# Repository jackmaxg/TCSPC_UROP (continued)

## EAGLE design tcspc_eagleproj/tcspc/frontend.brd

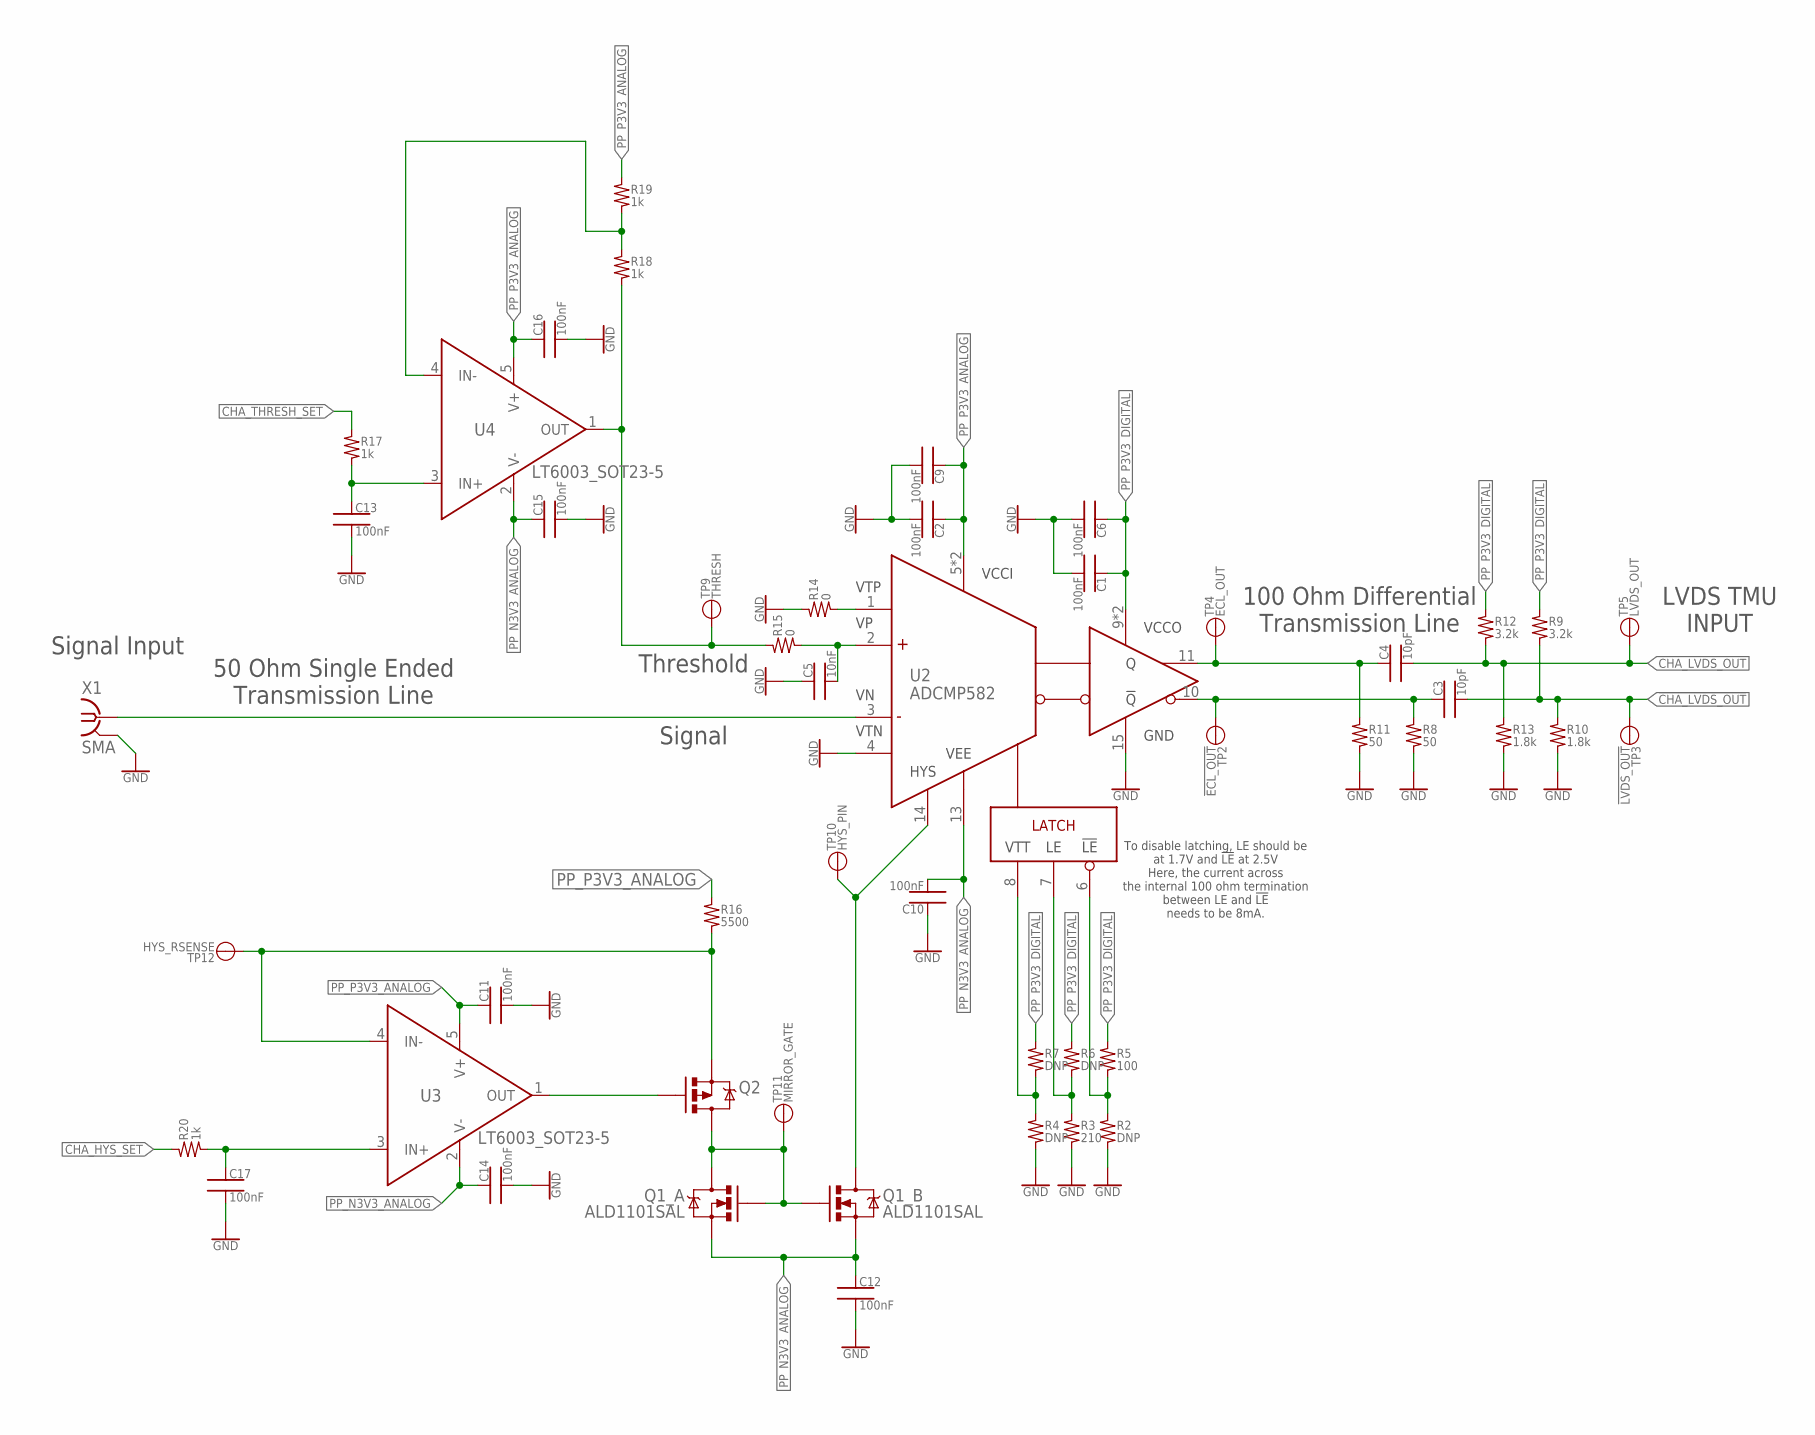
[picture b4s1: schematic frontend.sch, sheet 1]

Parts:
C1, C2, C6, C9, C10, C11, C12, C13, C14, C15, C16, C17: 100nF; 0402
C3, C4: 10pF; 0402
C5: 10nF; 0402
Q1: ALD1101SAL; SOIC_8
Q2: MOSFET_P-CHANNEL_SOT23-3; SOT23-3
R2, R4, R6, R7: DNP; 0402
R3: 210; 0402
R5: 100; 0402
R8, R11: 50; 0402
R9, R12: 3.2k; 0402
R10, R13: 1.8k; 0402
R14, R15: 0; 0402
R16: 5500; 0402
R17, R18, R19, R20: 1k; 0402
TP2: !ECL_OUT; TESTPOINT_PAD
TP3: !LVDS_OUT; TESTPOINT_PAD
TP4: ECL_OUT; TESTPOINT_PAD
TP5: LVDS_OUT; TESTPOINT_PAD
TP9: THRESH; 1X01
TP10: HYS_PIN; 1X01
TP11: MIRROR_GATE; 1X01
TP12: HYS_RSENSE; 1X01
U2: ADCMP582; QFN50P300X300X80-16N
U3, U4: LT6003_SOT23-5; SOT23-5
X1: SMA; J502-ND-142-0701-881/886

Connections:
!CHA_LVDS_OUT: C3.2, R9.2, R10.1, TP3.TP; also elsewhere on the board
CHA_HYS_SET: R20.1; also elsewhere on the board
CHA_LVDS_OUT: C4.2, R12.2, R13.1, TP5.TP; also elsewhere on the board
CHA_THRESH_SET: R17.1; also elsewhere on the board
GND: C1.2, C2.2, C5.1, C6.2, C9.2, C10.1, C11.2, C12.2, C13.2, C14.2, C15.2, C16.2, C17.2, R2.2, R3.2, R4.2, R8.2, R10.2, R11.2, R13.2, R14.1, U2.4 (VTN), U2.15 (GND), X1.G@1 (GND), X1.G@2 (GND), X1.G@3 (GND), X1.G@4 (GND); also elsewhere on the board
unnamed: Q2.2 (S), R16.2, TP12.1, U3.4 (IN-)
unnamed: Q1.2 (G), Q1.3 (D), Q1.6 (G), Q2.3 (D), TP11.1
unnamed: C3.1, R8.1, TP2.TP, U2.10 (!Q)
unnamed: C4.1, R11.1, TP4.TP, U2.11 (Q)
unnamed: R14.2, U2.1 (VTP)
unnamed: C13.1, R17.2, U4.3 (IN+)
unnamed: Q2.1 (G), U3.1 (OUT)
unnamed: R18.1, R19.2, U4.4 (IN-)
unnamed: R15.1, R18.2, TP9.1, U4.1 (OUT)
unnamed: C17.1, R20.2, U3.3 (IN+)
unnamed: U2.3 (VN), X1.1
unnamed: C5.2, R15.2, U2.2 (VP)
unnamed: R4.1, R7.2, U2.8 (VTT)
unnamed: R3.1, R6.2, U2.7 (LE)
unnamed: R2.1, R5.2, U2.6 (!LE)
unnamed: Q1.5 (D), TP10.1, U2.14 (HYS)
PP_N3V3_ANALOG: C10.2, C12.1, C14.1, C15.1, Q1.1 (S), Q1.7 (S), Q1.8 (S), U2.13 (VEE), U3.2 (V-), U4.2 (V-); also elsewhere on the board
PP_P3V3_ANALOG: C2.1, C9.1, C11.1, C16.1, R16.1, R19.1, U2.5 (VCCI), U2.16 (VCCI), U3.5 (V+), U4.5 (V+); also elsewhere on the board
PP_P3V3_DIGITAL: C1.1, C6.1, R5.1, R6.1, R7.1, R9.1, R12.1, U2.9 (VCCO), U2.12 (VCCO); also elsewhere on the board

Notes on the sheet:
LVDS TMU INPUT
Threshold
Signal Input
100 Ohm Differential Transmission Line
50 Ohm Single Ended Transmission Line
Signal
To disable latching, LE should be at 1.7V and !LE! at 2.5V Here, the current across the internal 100 ohm termination between LE and !LE! needs to be 8mA.

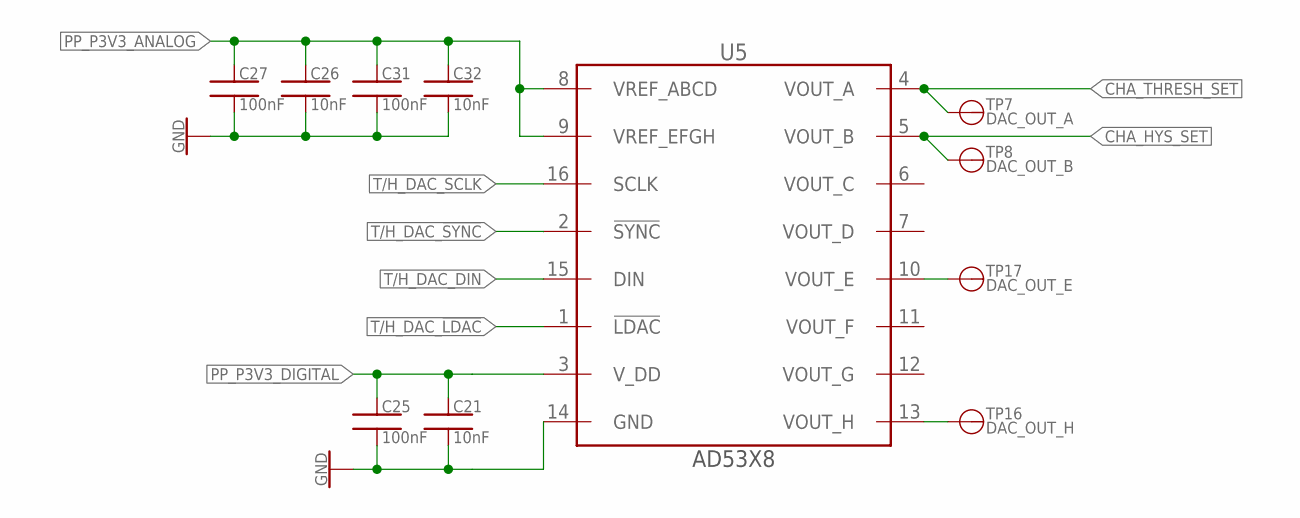
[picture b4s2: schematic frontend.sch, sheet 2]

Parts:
C21, C26, C32: 10nF; 0402
C25, C27, C31: 100nF; 0402
TP7: DAC_OUT_A; 1X01
TP8: DAC_OUT_B; 1X01
TP16: DAC_OUT_H; 1X01
TP17: DAC_OUT_E; 1X01
U5: AD53X8; TSSOP-16

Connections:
CHA_HYS_SET: TP8.1, U5.5 (VOUT_B); also elsewhere on the board
CHA_THRESH_SET: TP7.1, U5.4 (VOUT_A); also elsewhere on the board
GND: C21.2, C25.2, C26.2, C27.2, C31.2, C32.2, U5.14 (GND); also elsewhere on the board
unnamed: TP17.1, U5.10 (VOUT_E)
unnamed: TP16.1, U5.13 (VOUT_H)
PP_P3V3_ANALOG: C26.1, C27.1, C31.1, C32.1, U5.8 (VREF_ABCD), U5.9 (VREF_EFGH); also elsewhere on the board
PP_P3V3_DIGITAL: C21.1, C25.1, U5.3 (V_DD); also elsewhere on the board
T/H_DAC_!LDAC!: U5.1 (!LDAC); also elsewhere on the board
T/H_DAC_!SYNC!: U5.2 (!SYNC); also elsewhere on the board
T/H_DAC_DIN: U5.15 (DIN); also elsewhere on the board
T/H_DAC_SCLK: U5.16 (SCLK); also elsewhere on the board

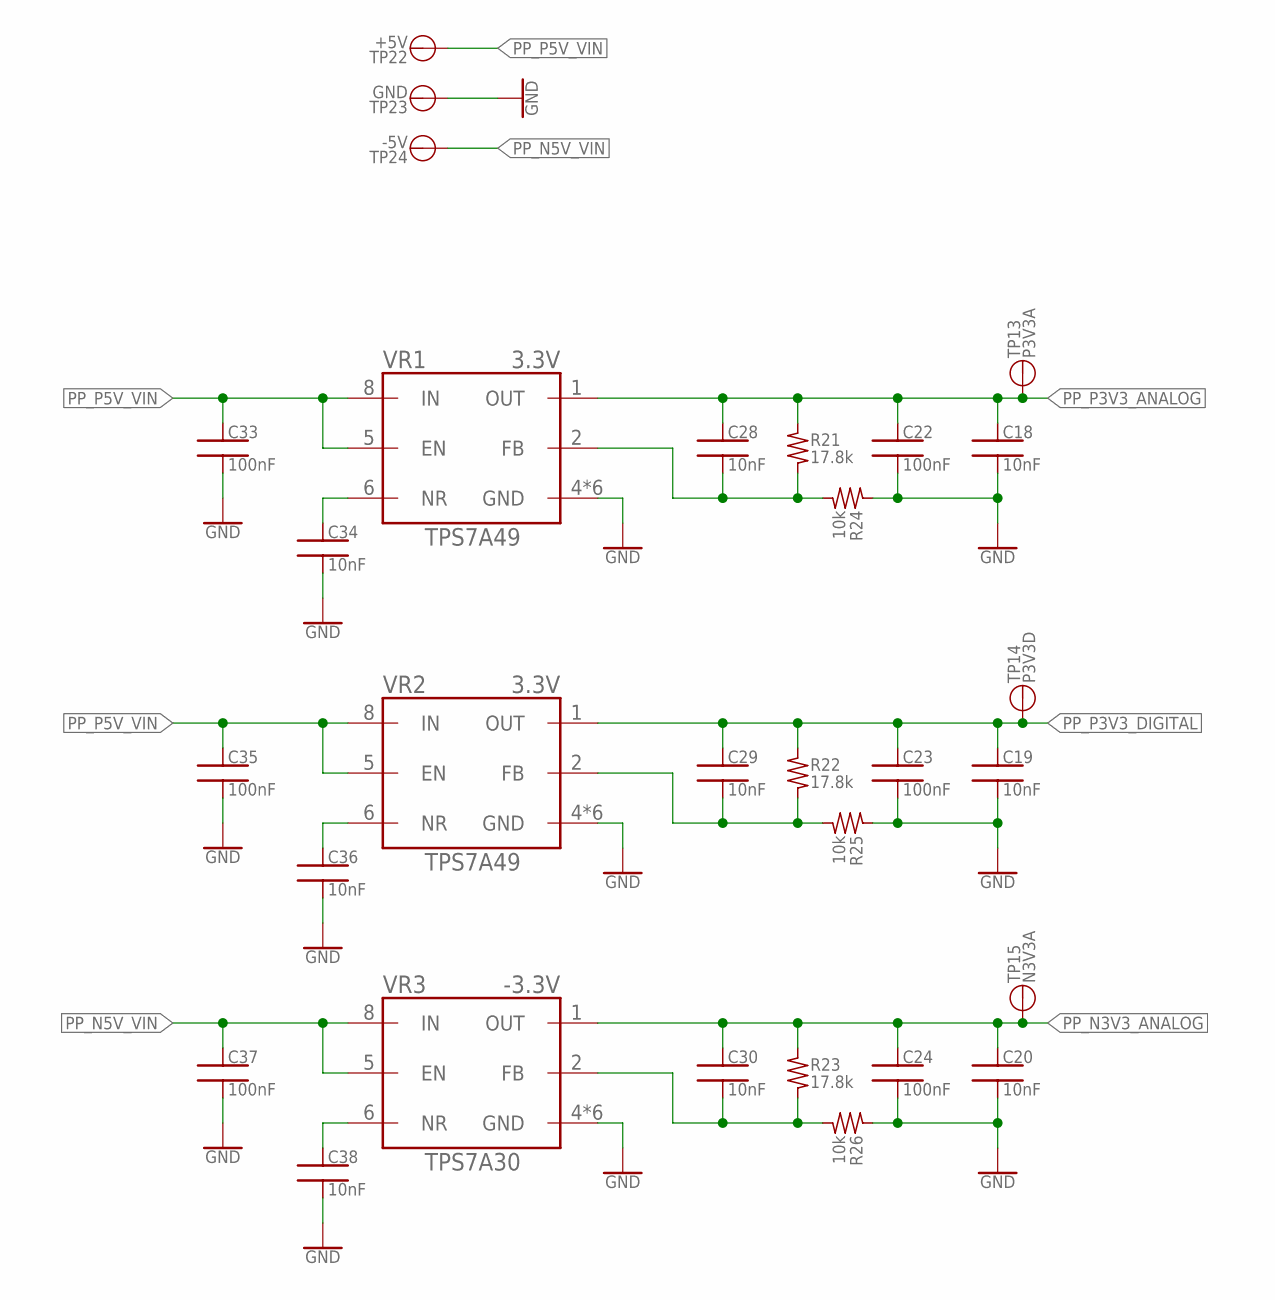
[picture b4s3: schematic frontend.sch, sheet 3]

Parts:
C18, C19, C20, C28, C29, C30, C34, C36, C38: 10nF; 0402
C22, C23, C24, C33, C35, C37: 100nF; 0402
R21, R22, R23: 17.8k; 0402
R24, R25, R26: 10k; 0402
TP13: P3V3A; 1X01
TP14: P3V3D; 1X01
TP15: N3V3A; 1X01
TP22: +5V; 1X01
TP23: GND; 1X01
TP24: -5V; 1X01
VR1, VR2: 3.3V; VSON
VR3: -3.3V; VSON

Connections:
GND: C18.2, C19.2, C20.2, C22.2, C23.2, C24.2, C33.2, C34.2, C35.2, C36.2, C37.2, C38.2, R24.1, R25.1, R26.1, TP23.1, VR1.4 (GND), VR1.TP (GND), VR1.TP_A (GND), VR1.TP_B (GND), VR1.TP_C (GND), VR1.TP_D (GND), VR2.4 (GND), VR2.TP (GND), VR2.TP_A (GND), VR2.TP_B (GND), VR2.TP_C (GND), VR2.TP_D (GND), VR3.4 (GND), VR3.TP (GND), VR3.TP_A (GND), VR3.TP_B (GND), VR3.TP_C (GND), VR3.TP_D (GND); also elsewhere on the board
unnamed: C30.2, R23.2, R26.2, VR3.2 (FB)
unnamed: C28.2, R21.2, R24.2, VR1.2 (FB)
unnamed: C36.1, VR2.6 (NR)
unnamed: C34.1, VR1.6 (NR)
unnamed: C29.2, R22.2, R25.2, VR2.2 (FB)
unnamed: C38.1, VR3.6 (NR)
PP_N3V3_ANALOG: C20.1, C24.1, C30.1, R23.1, TP15.1, VR3.1 (OUT); also elsewhere on the board
PP_N5V_VIN: C37.1, TP24.1, VR3.5 (EN), VR3.8 (IN)
PP_P3V3_ANALOG: C18.1, C22.1, C28.1, R21.1, TP13.1, VR1.1 (OUT); also elsewhere on the board
PP_P3V3_DIGITAL: C19.1, C23.1, C29.1, R22.1, TP14.1, VR2.1 (OUT); also elsewhere on the board
PP_P5V_VIN: C33.1, C35.1, TP22.1, VR1.5 (EN), VR1.8 (IN), VR2.5 (EN), VR2.8 (IN)

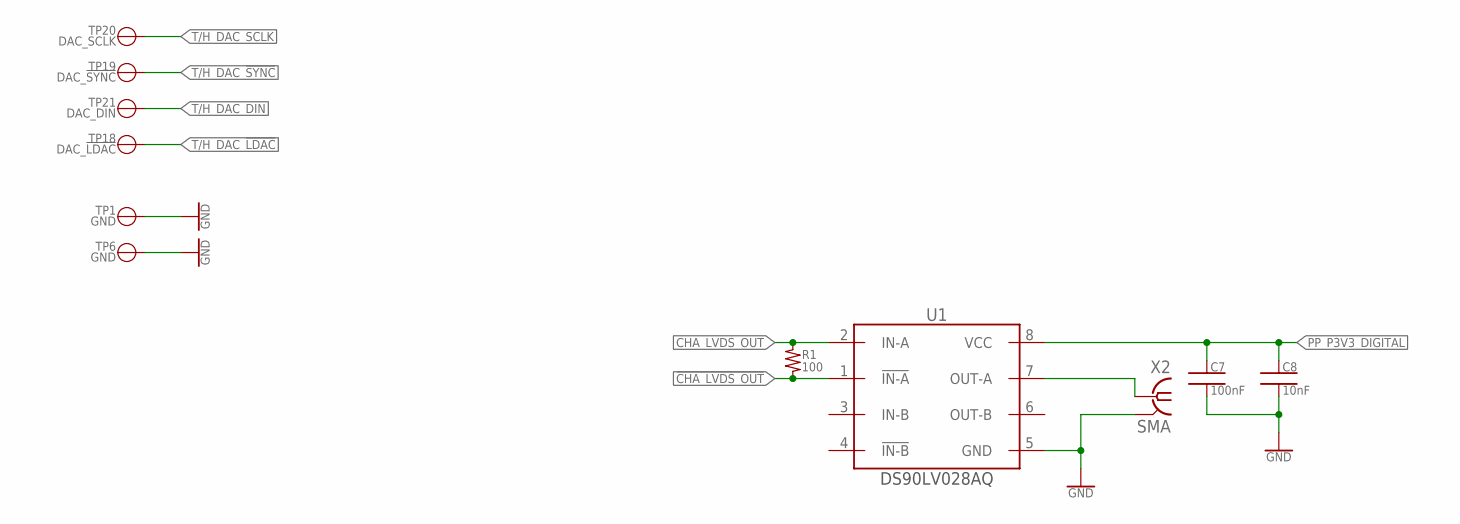
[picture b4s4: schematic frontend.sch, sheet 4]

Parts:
C7: 100nF; 0402
C8: 10nF; 0402
R1: 100; 0402
TP1, TP6: GND; 1X01
TP18: DAC_!LDAC!; 1X01
TP19: DAC_!SYNC!; 1X01
TP20: DAC_SCLK; 1X01
TP21: DAC_DIN; 1X01
U1: DS90LV028AQ; SOIC_8
X2: SMA; J502-ND-142-0701-881/886

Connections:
!CHA_LVDS_OUT: R1.2, U1.1 (!IN-A); also elsewhere on the board
CHA_LVDS_OUT: R1.1, U1.2 (IN-A); also elsewhere on the board
GND: C7.2, C8.2, TP1.1, TP6.1, U1.5 (GND), X2.G@1 (GND), X2.G@2 (GND), X2.G@3 (GND), X2.G@4 (GND); also elsewhere on the board
unnamed: U1.7 (OUT-A), X2.1
PP_P3V3_DIGITAL: C7.1, C8.1, U1.8 (VCC); also elsewhere on the board
T/H_DAC_!LDAC!: TP18.1; also elsewhere on the board
T/H_DAC_!SYNC!: TP19.1; also elsewhere on the board
T/H_DAC_DIN: TP21.1; also elsewhere on the board
T/H_DAC_SCLK: TP20.1; also elsewhere on the board

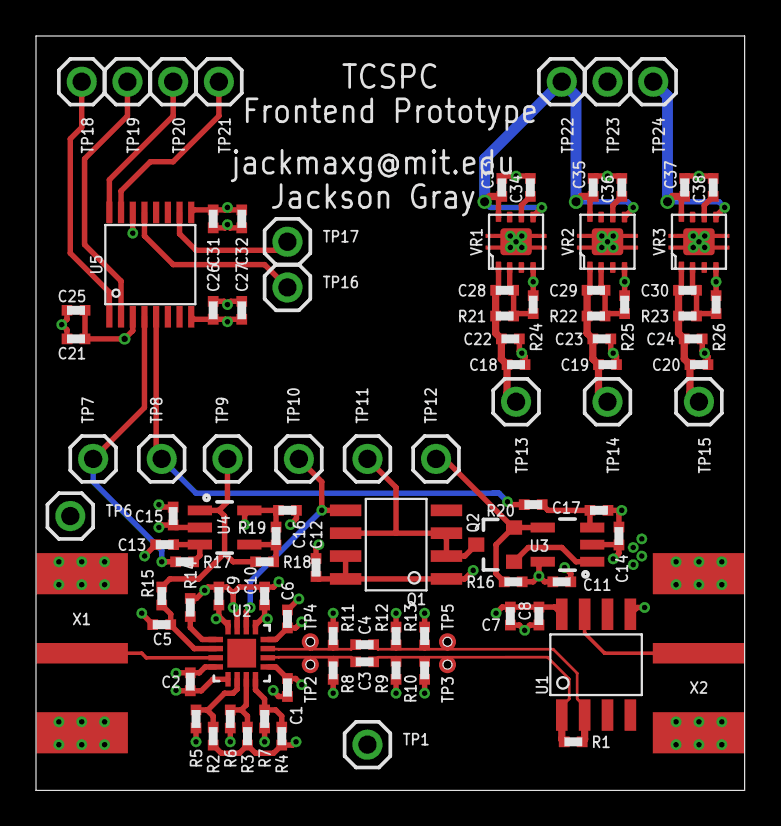
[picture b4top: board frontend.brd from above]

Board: 4 copper layers, 39.4 x 41.9 mm, 100 parts (0 on the bottom side), 39 nets.

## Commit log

2018-05-28 Added gitignore file
2018-05-28 added new project and empty schematic
2018-05-28 updated readme file
2018-05-29 Made a project library and added the THS788 to it. Added a frame to the schematic.
2018-05-29 Added the THS788 to the sch, made a simple brd with the 788 on it. Created a gitattributes file so I don't keep getting crlf messages for eagle files.
2018-05-29 added the SiT5021 Oscillator to the library
2018-05-29 added the MCP4725 DAC to the library
2018-05-29 removed the bottom side thermal pad from the THS788
2018-05-29 Added a few simple RCL symbols into the library and tweaked them a bit.
2018-05-29 copied over the threaded mounts from kramnik's lib
2018-05-30 threw a couple SMAs and DACs onto the schematic
2018-05-30 pulled kramnik's comparator into the project library and tweaked some bits, made RES and CAP devices
2018-06-11 moved the library into the project directory
2018-06-13 Added 0402 option to the library, tweaked the front end, organized and ordered the front end on the board, added a bunch of bypass caps for the TDC.
2018-06-20 Modified the 0402 package to have layout indicators, so I can leave myself some room for when I assemble the board. Twiddled the layout of the frontend, so that I can try get a frontend demo board ou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
2018-06-29 not 100% sure what changes got made here but there was a good chunk of progress nonetheless
2018-06-29 Started making the frontend test board, made a dbl off the original schematic and made a new schematic for it. Properly disposed of the comparator latching with resistors. Designed, simulated and imp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
2018-07-01 added the postregs to the frontend schematic, and also the output LVDS to TTL converter, only major thing left is to add testpoints places.
2018-07-10 The frontend schematic seems done, added more testpoints and replaced the single dacs with a eight channel 12 bit dac, and added a spot to stick datasheets for the parts
2018-07-11 stuffed another datasheet into the folder, made some small tweaks to the schematic, created a new brd file and started organizing parts for routing. Fixed the small dot test pad and added a small dri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
2018-07-12 Added a termination resistor to the LVDS to TTL reciever, changed a few layers on the SMA coax connector, finished up the board layout, generated gerbers to send to 3PCB.
2018-08-06 adding the bom for the frontend and some datasheets and learning materials bits
2018-08-06 added .csv to the gitattributes file
2018-08-06 Did more LTSpice things, testing tapping off the ECL output lines for DC status, and also added some vivado gitignores things
2018-08-06 adding all the vivado stuff i've been neglecting to add to git bc its a pain
2018-08-06 Added and have been working on the THS788 carrier board for a while without committing it
2018-08-10 Did some investigation about the threshold setting opamp in the V1 frontend, made simulations and fixed the issue
2018-08-10 Did a little more work on the THS788 carrier, routed a few more HS diff signals
2018-08-10 started work on the new simplified frontend
2018-08-10 turned the frontend into a useful designblock, ready to be pased all over the tcspc board
2018-08-10 small tweaks to the dbl so that I could start putting four of them onto the main board, and then I did just that.
2018-08-14 created an FPGA device in the library, stuck it on the board and hooked up the various power pins to their nets. I also added the linear postregs and DAC to the schematic, and did some power calcs.
